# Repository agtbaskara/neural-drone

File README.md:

# Neural Drone
flight controller with a mix of neural network

## Requirement
- Raspberry Pi 4 Model B
- Flight Controller HAT

## Notes
- TODO

## Install Adafruit Blinka
https://learn.adafruit.com/circuitpython-on-raspberrypi-linux/installing-circuitpython-on-raspberry-pi

## Enable I2C
https://learn.adafruit.com/adafruits-raspberry-pi-lesson-4-gpio-setup/configuring-i2c

## Enable SPI
https://learn.adafruit.com/adafruits-raspberry-pi-lesson-4-gpio-setup/configuring-spi

## Test Program Notes
- blinkatest.py
Test Blinka Installation I2C, SPI, and GPIO access
https://learn.adafruit.com/circuitpython-on-raspberrypi-linux/installing-circuitpython-on-raspberry-pi
- bmp388test.py
Test BMP388 Barometer
https://learn.adafruit.com/adafruit-bmp388/python-circuitpython
- bno055test.py
Test BNO055 IMU
https://learn.adafruit.com/adafruit-bno055-absolute-orientation-sensor/python-circuitpython
- gpstest.py
Test GPS
- ms5611test.py
Test MS5611 Barometer
- motortest.py
Test 4 Brushless Motor
- pca9685test.py
Test PCA9685 I2C PWM Driver
https://learn.adafruit.com/16-channel-pwm-servo-driver/python-circuitpython
- sbustest.py
Test SBUS

Install GPS
pip3 install pynmea2

Enable tty access
https://www.raspberrypi.org/forums/viewtopic.php?t=180254

enable additional serial port
https://lb.raspberrypi.org/forums/viewtopic.php?t=244827

enable_uart=1
dtoverlay=pi3-miniuart-bt
dtoverlay=uart5
dtoverlay=uart4
dtoverlay=uart3
dtoverlay=uart2

## Reference
- CoppeliaSim B0-based remote API http://www.coppeliarobotics.com/helpFiles/en/b0RemoteApi-python.htm
- Pygame Joystick https://www.pygame.org/docs/ref/joystick.html
- SBUS to USB https://github.com/agtbaskara/sbusjoystick-ardupilot-sitl

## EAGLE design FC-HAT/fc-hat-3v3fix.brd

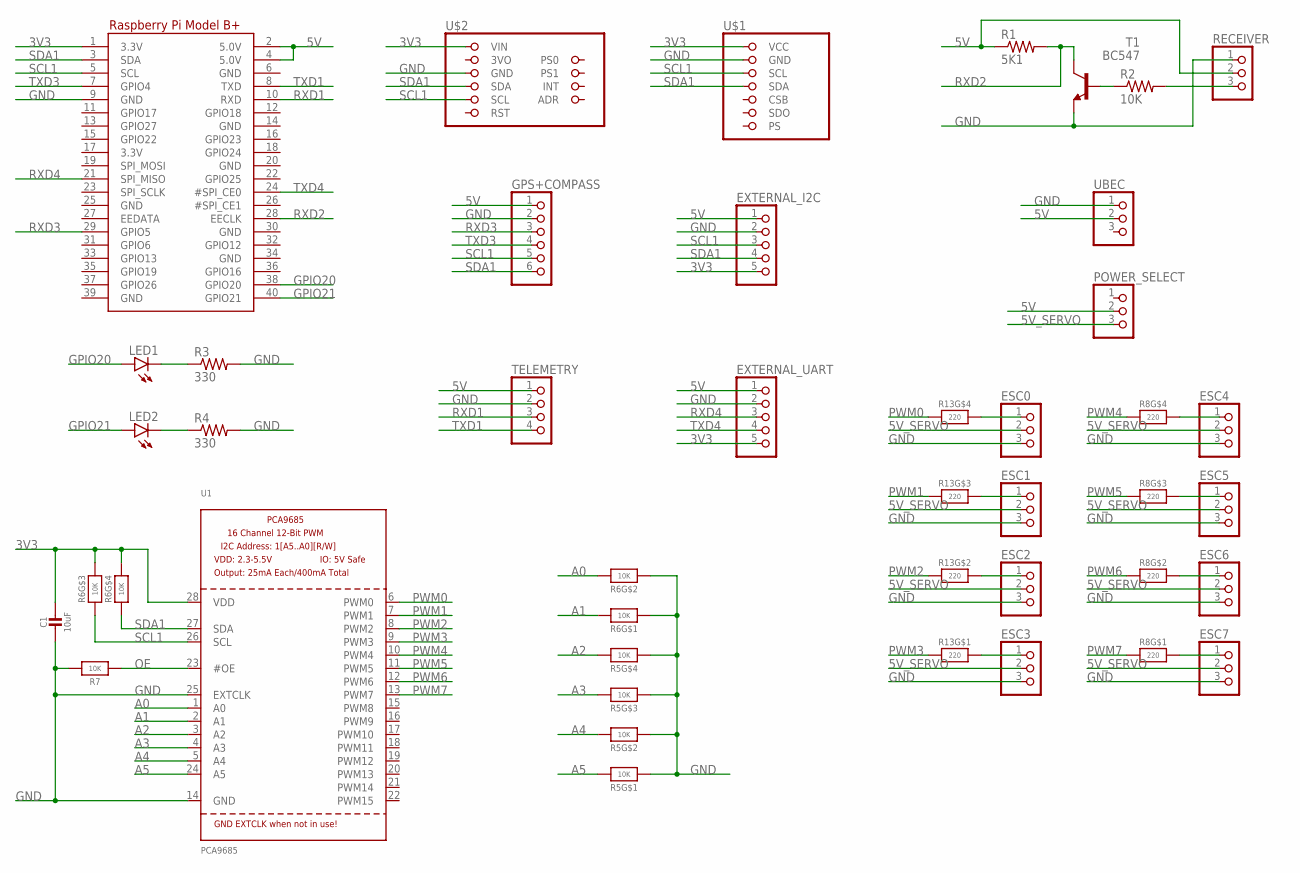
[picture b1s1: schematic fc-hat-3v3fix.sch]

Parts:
C1: 10uF; 0805-NO
ESC0, ESC1, ESC2, ESC3, ESC4, ESC5, ESC6, ESC7: PINHD-1X31X03_ROUND; 1X03_ROUND
EXTERNAL_I2C: PINHD-1X51X05_ROUND; 1X05_ROUND
EXTERNAL_UART: PINHD-1X51X05_ROUND; 1X05_ROUND
GPS+COMPASS: PINHD-1X61X06_ROUND; 1X06_ROUND
LED1, LED2: LED5MM
POWER_SELECT: PINHD-1X31X03_ROUND; 1X03_ROUND
R1: 5K1; 0207/10
R2: 10K; 0207/10
R3, R4: 330; 0207/10
R5, R6: 10K; RESPACK_4X0603
R7: 10K; 0805-NO
R8, R13: 220; RESPACK_4X0603
RECEIVER: PINHD-1X31X03_ROUND; 1X03_ROUND
RPI1: MICROBUILDER_RASPBERRYPI_BPLUS_HATNOSLOTS; MICROBUILDER_PI_HAT_NOSLOTS
T1: BC547; TO92
TELEMETRY: PINHD-1X41X04_ROUND; 1X04_ROUND
U1: PCA9685; TSSOP28
U$1: GY-63
U$2: BNO055
UBEC: PINHD-1X31X03_ROUND; 1X03_ROUND

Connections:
3V3: C1.1, EXTERNAL_I2C.5, EXTERNAL_UART.5, R6.5 (2), R6.6 (2), RPI1.1 (3.3V), U1.28 (VDD), U$1.VCC, U$2.VIN
5V: EXTERNAL_I2C.1, EXTERNAL_UART.1, GPS+COMPASS.1, POWER_SELECT.2, R1.1, RECEIVER.2, RPI1.2 (5.0V), RPI1.4 (5.0V), TELEMETRY.1, UBEC.2
5V_SERVO: ESC0.2, ESC1.2, ESC2.2, ESC3.2, ESC4.2, ESC5.2, ESC6.2, ESC7.2, POWER_SELECT.3
A0: R6.7 (2), U1.1 (A0)
A1: R6.8 (2), U1.2 (A1)
A2: R5.5 (2), U1.3 (A2)
A3: R5.6 (2), U1.4 (A3)
A4: R5.7 (2), U1.5 (A4)
A5: R5.8 (2), U1.24 (A5)
GND: C1.2, ESC0.3, ESC1.3, ESC2.3, ESC3.3, ESC4.3, ESC5.3, ESC6.3, ESC7.3, EXTERNAL_I2C.2, EXTERNAL_UART.2, GPS+COMPASS.2, R3.2, R4.2, R5.1, R5.2 (1), R5.3 (1), R5.4 (1), R6.1, R6.2 (1), R7.2, RECEIVER.1, RPI1.9 (GND), T1.1 (E), TELEMETRY.2, U1.14 (GND), U1.25 (EXTCLK), U$1.GND, U$2.GND, UBEC.1
GPIO20: LED1.A, RPI1.38 (GPIO20)
GPIO21: LED2.A, RPI1.40 (GPIO21)
unnamed: R2.2, RECEIVER.3
unnamed: R2.1, T1.2 (B)
unnamed: LED1.K (C), R3.1
unnamed: LED2.K (C), R4.1
unnamed: ESC7.1, R8.8 (2)
unnamed: ESC6.1, R8.7 (2)
unnamed: ESC5.1, R8.6 (2)
unnamed: ESC4.1, R8.5 (2)
unnamed: ESC3.1, R13.8 (2)
unnamed: ESC2.1, R13.7 (2)
unnamed: ESC1.1, R13.6 (2)
unnamed: ESC0.1, R13.5 (2)
OE: R7.1, U1.23 (#OE)
PWM0: R13.4 (1), U1.6 (PWM0)
PWM1: R13.3 (1), U1.7 (PWM1)
PWM2: R13.2 (1), U1.8 (PWM2)
PWM3: R13.1, U1.9 (PWM3)
PWM4: R8.4 (1), U1.10 (PWM4)
PWM5: R8.3 (1), U1.11 (PWM5)
PWM6: R8.2 (1), U1.12 (PWM6)
PWM7: R8.1, U1.13 (PWM7)
RXD1: RPI1.10 (RXD), TELEMETRY.3
RXD2: R1.2, RPI1.28 (EECLK), T1.3 (C)
RXD3: GPS+COMPASS.3, RPI1.29 (GPIO5)
RXD4: EXTERNAL_UART.3, RPI1.21 (SPI_MISO)
SCL1: EXTERNAL_I2C.3, GPS+COMPASS.5, R6.3 (1), RPI1.5 (SCL), U1.26 (SCL), U$1.SCL, U$2.SCL
SDA1: EXTERNAL_I2C.4, GPS+COMPASS.6, R6.4 (1), RPI1.3 (SDA), U1.27 (SDA), U$1.SDA, U$2.SDA
TXD1: RPI1.8 (TXD), TELEMETRY.4
TXD3: GPS+COMPASS.4, RPI1.7 (GPIO4)
TXD4: EXTERNAL_UART.4, RPI1.24 (#SPI_CE0)

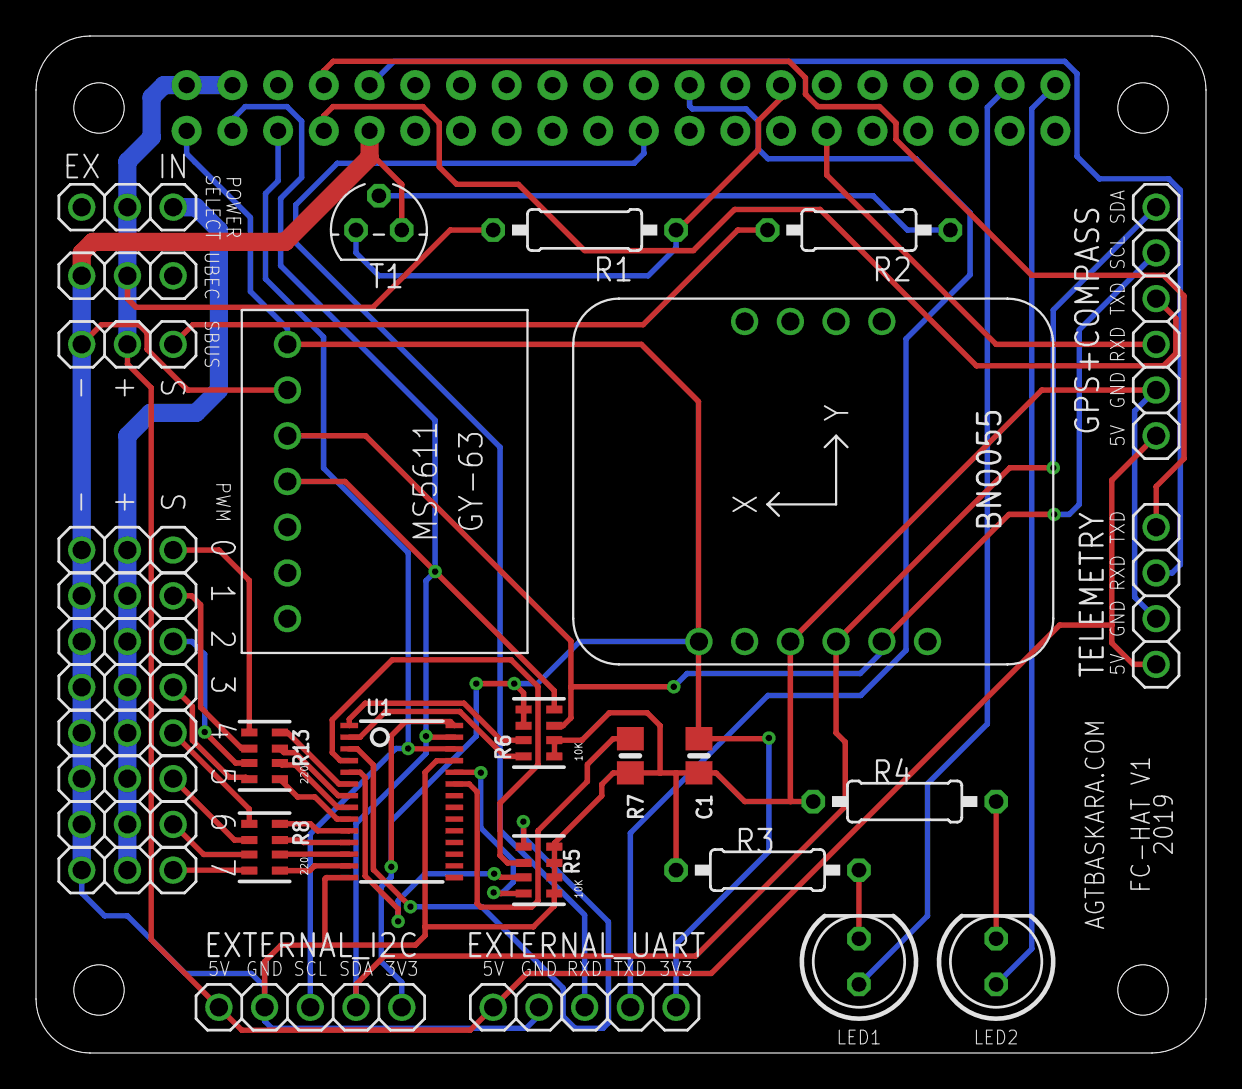
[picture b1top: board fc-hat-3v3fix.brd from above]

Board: 2 copper layers, 65.0 x 56.5 mm, 32 parts (0 on the bottom side), 42 nets.

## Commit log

2019-12-13 Add Initial Code
    Working Sensor Reading from Simulator
    Working Remote Input
    Working Actuator Output to Simulator
2019-12-13 Fix Remote Zero Value Error
2019-12-16 Add F450 Model
2020-02-11 Seperate RL Program, add test program
2020-02-11 Add ledtest.py
2020-02-11 Add telemetry test
2020-02-11 Add FC-HAT PCB File
